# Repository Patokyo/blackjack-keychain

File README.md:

# Blackjack Keychain

A credit-card-sized blackjack strategy trainer. An ATmega328P deals a
six-deck shoe, you answer each decision with the on-board buttons, and
the firmware marks every answer correct or incorrect against basic
strategy before playing the hand out.

This is work in progress: the game logic and the serial log work, the
four-digit display and the LEDs are wired and mapped but not driven
yet.

## Repository layout

```
hardware/
  blackjack-keychain.kicad_pro      KiCad 10 project
  blackjack-keychain.kicad_sch      schematic, single sheet
  blackjack-keychain.kicad_pcb      board, 2 layer
  blackjack-keychain.net            netlist exported from the schematic
  fp-lib-table                      project footprint library table
  custom_footprint_library.pretty   project footprints (display, ISP pads)
  fabrication/                      gerbers, drills, job file, fab zip
firmware/
  blackjack-keychain/
    blackjack-keychain.ino        the sketch
  nano-blackjack/
    nano-blackjack.ino            the same game, remapped for a Nano
  nano-display-test/
    nano-display-test.ino         display wiring check for a Nano
virtual/
  index.html                        the board in a browser
  game.js, ui.js                    game engine, display and controls
  board-blue.svg, board-red.svg     front of the PCB, generated per mask colour
  make_board.py                     plots those from hardware/fabrication
```

The KiCad project, its netlist and its outputs stay together under
`hardware/` so the project opens with everything it needs in one
place. `hardware/fabrication/` holds the last set of outputs sent to
a board house; regenerating them means re-plotting from KiCad, not
editing them by hand. The virtual board is drawn from the same files:
`python3 virtual/make_board.py` re-plots `virtual/board-blue.svg` and
`virtual/board-red.svg` after a re-plot, so the browser keeps matching
the board.

## Hardware

| | |
|---|---|
| Board | 50 x 70 mm, 2 layer, 1.6 mm, 3.5 mm corner radius |
| MCU | ATmega328P-AU, TQFP-32, 5 V from USB-C, internal 8 MHz RC, no crystal |
| Display | CC56-12EWA, 0.28" four digit, common cathode, one NPN low side switch per digit |
| Indicators | 7 LEDs, active high through 330R |
| Input | 5 tactile buttons on two resistor ladders, plus SW6 as a strap |
| Programming | 2x03 ISP pads |

The board is powered from the USB-C socket. There is no USB-serial
chip on it, so the ISP pads are the only way to program it.

Pin map, as used by the firmware:

| Function | Pin | Pad |
|---|---|---|
| Correct / wrong / lose / push LEDs | D2 / D1 / D3 / D4 | 32 / 31 / 1 / 2 |
| Soft / pair / win LEDs | A1 / A3 / PB6 | 24 / 26 / 7 |
| Buttons, hit/stand/double ladder | A4 | 27 |
| Buttons, split/bank ladder | A5 | 28 |
| Display segments a-g, dp | D12, D6, D8, D11, D13, D10, D7, D9 | 16, 10, 12, 15, 17, 14, 11, 13 |
| Display digit drives Q1-Q4 | PB7, A0, D5, A2 | 8, 23, 9, 25 |
| SW6 strap | D0 | 30 |
| Serial TX | D1 (shared with the wrong LED) | 31 |

Two consequences of that netlist are worth knowing before flashing:
serial transmit shares a pin with an LED, so that LED glows between
bytes and flickers during output, and serial receive is held at +5 V or
GND by SW6, so the port cannot be typed into on an assembled board.
The buttons are the only input.

## Firmware

Open `firmware/blackjack-keychain/blackjack-keychain.ino` in the
Arduino IDE. The folder name matches the sketch name, as the IDE
requires.

- Build with `F_CPU = 8000000L` — MiniCore's ATmega328 at "8 MHz
  internal", or a Pro Mini 3.3 V/8 MHz board definition.
- Low fuse `0xE2`, with CKDIV8 unprogrammed. A part straight from the
  factory divides the internal oscillator down to 1 MHz, which plays
  the game eight times too slowly and garbles the serial output.
- Serial monitor at 9600 baud.

Rules: six deck shoe reshuffled between hands, dealer stands on soft
17, double on any first two cards, double after split allowed, up to
four hands by splitting (no resplitting aces, split aces get one card),
two card 21 is a natural that beats a made 21. Start with $100, a flat
$10 a hand, and the game ends when $10 can no longer be covered.

Controls are `H` (hit), `S` (stand), `D` (double) and `P` (split),
from the buttons or typed into the serial monitor if SW6 is left off
the board. The bank button is wired but has no game action yet.

## Building the hardware

The schematic and board reference one project-specific footprint
library, `custom_footprint_library`, which provides the 7 segment
display and the ISP pads. Both footprints are committed in
`hardware/custom_footprint_library.pretty/`, and `hardware/fp-lib-table`
maps the nickname onto that folder with `${KIPRJMOD}`, so the project
resolves them straight from a clone without any library setup.

To regenerate the outputs in `hardware/fabrication/`, plot from KiCad
with the same layer set currently committed: F.Cu, B.Cu, F.Paste,
B.Paste, F.Silkscreen, B.Silkscreen, F.Mask, B.Mask, Edge.Cuts, plus
the PTH and NPTH drill files.

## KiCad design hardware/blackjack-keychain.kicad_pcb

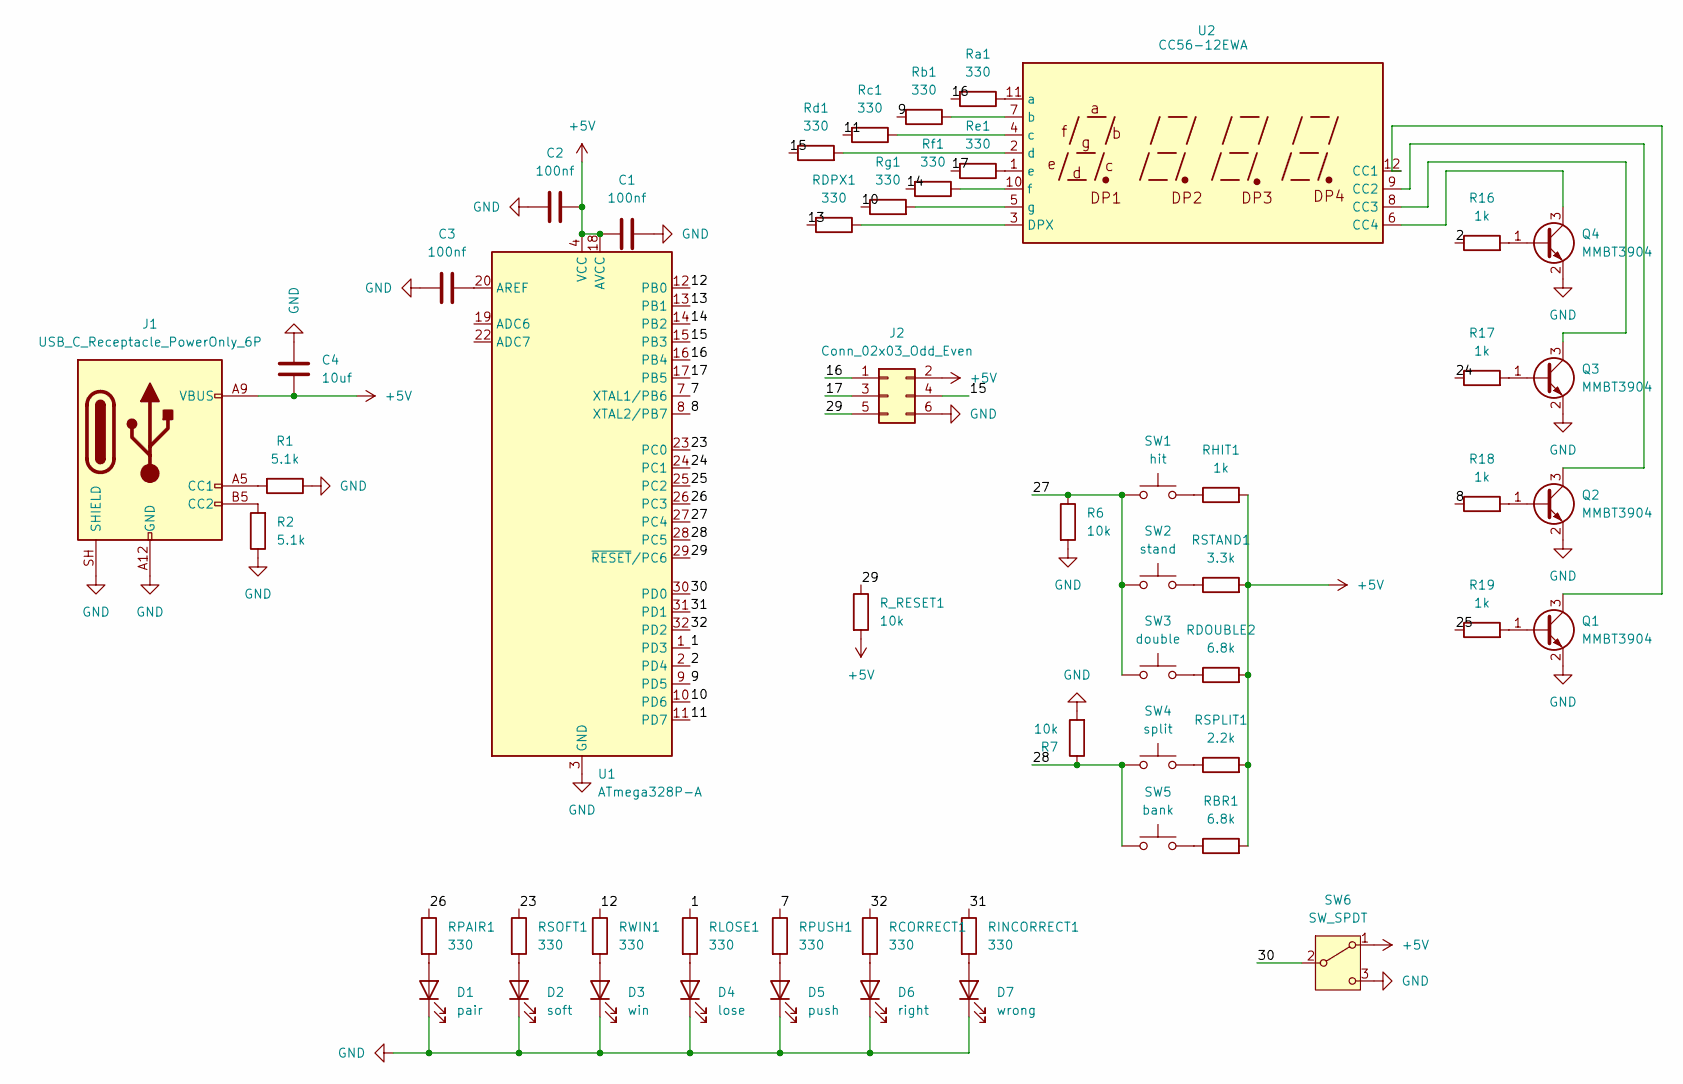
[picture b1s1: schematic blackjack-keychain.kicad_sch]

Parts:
C1, C2, C3: 100nf; C_0805_2012Metric_Pad1.18x1.45mm_HandSolder
C4: 10uf; C_0805_2012Metric_Pad1.18x1.45mm_HandSolder
D1: pair; LED_1210_3225Metric_Pad1.42x2.65mm_HandSolder
D2: soft; LED_1210_3225Metric_Pad1.42x2.65mm_HandSolder
D3: win; LED_1210_3225Metric_Pad1.42x2.65mm_HandSolder
D4: lose; LED_1210_3225Metric_Pad1.42x2.65mm_HandSolder
D5: push; LED_1210_3225Metric_Pad1.42x2.65mm_HandSolder
D6: right; LED_1210_3225Metric_Pad1.42x2.65mm_HandSolder
D7: wrong; LED_1210_3225Metric_Pad1.42x2.65mm_HandSolder
J1: USB_C_Receptacle_PowerOnly_6P; USB_C_Receptacle_GCT_USB4125-xx-x-0190_6P_TopMnt_Horizontal
J2: Conn_02x03_Odd_Even; ISP_2x03_Pads
Q1, Q2, Q3, Q4: MMBT3904; SOT-23
R1, R2: 5.1k; R_0805_2012Metric_Pad1.20x1.40mm_HandSolder
R6, R7: 10k; R_0805_2012Metric_Pad1.20x1.40mm_HandSolder
R16, R17, R18, R19: 1k; R_0805_2012Metric_Pad1.20x1.40mm_HandSolder
RBR1: 6.8k; R_0805_2012Metric_Pad1.20x1.40mm_HandSolder
RCORRECT1: 330; R_0805_2012Metric_Pad1.20x1.40mm_HandSolder
RDOUBLE2: 6.8k; R_0805_2012Metric_Pad1.20x1.40mm_HandSolder
RDPX1: 330; R_0805_2012Metric_Pad1.20x1.40mm_HandSolder
RHIT1: 1k; R_0805_2012Metric_Pad1.20x1.40mm_HandSolder
RINCORRECT1: 330; R_0805_2012Metric_Pad1.20x1.40mm_HandSolder
RLOSE1: 330; R_0805_2012Metric_Pad1.20x1.40mm_HandSolder
RPAIR1: 330; R_0805_2012Metric_Pad1.20x1.40mm_HandSolder
RPUSH1: 330; R_0805_2012Metric_Pad1.20x1.40mm_HandSolder
RSOFT1: 330; R_0805_2012Metric_Pad1.20x1.40mm_HandSolder
RSPLIT1: 2.2k; R_0805_2012Metric_Pad1.20x1.40mm_HandSolder
RSTAND1: 3.3k; R_0805_2012Metric_Pad1.20x1.40mm_HandSolder
RWIN1: 330; R_0805_2012Metric_Pad1.20x1.40mm_HandSolder
R_RESET1: 10k; R_0805_2012Metric_Pad1.20x1.40mm_HandSolder
Ra1: 330; R_0805_2012Metric_Pad1.20x1.40mm_HandSolder
Rb1: 330; R_0805_2012Metric_Pad1.20x1.40mm_HandSolder
Rc1: 330; R_0805_2012Metric_Pad1.20x1.40mm_HandSolder
Rd1: 330; R_0805_2012Metric_Pad1.20x1.40mm_HandSolder
Re1: 330; R_0805_2012Metric_Pad1.20x1.40mm_HandSolder
Rf1: 330; R_0805_2012Metric_Pad1.20x1.40mm_HandSolder
Rg1: 330; R_0805_2012Metric_Pad1.20x1.40mm_HandSolder
SW1: hit; SW_Tactile_SPST_NO_Straight_CK_PTS636Sx25SMTRLFS
SW2: stand; SW_Tactile_SPST_NO_Straight_CK_PTS636Sx25SMTRLFS
SW3: double; SW_Tactile_SPST_NO_Straight_CK_PTS636Sx25SMTRLFS
SW4: split; SW_Tactile_SPST_NO_Straight_CK_PTS636Sx25SMTRLFS
SW5: bank; SW_Tactile_SPST_NO_Straight_CK_PTS636Sx25SMTRLFS
SW6: SW_SPDT; SW_SPDT_Shouhan_MSK12C02
U1: ATmega328P-A; TQFP-32_7x7mm_P0.8mm
U2: CC56-12EWA; 7_Segment_Display-4_bit-0.28Inch

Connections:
+5V: C1.1, C2.1, C4.1, J1.A9 (VBUS), J1.B9 (VBUS), J2.2, RBR1.2, RDOUBLE2.2, RHIT1.2, RSPLIT1.2, RSTAND1.2, R_RESET1.2, SW6.1 (A), U1.4 (VCC), U1.6 (VCC), U1.18 (AVCC)
/1: RLOSE1.1, U1.1 (PD3)
/2: R16.1, U1.2 (PD4)
/7: RPUSH1.1, U1.7 (XTAL1/PB6)
/8: R18.1, U1.8 (XTAL2/PB7)
/9: Rb1.2, U1.9 (PD5)
/10: Rg1.1, U1.10 (PD6)
/11: Rc1.2, U1.11 (PD7)
/12: RWIN1.1, U1.12 (PB0)
/13: RDPX1.2, U1.13 (PB1)
/14: Rf1.2, U1.14 (PB2)
/15: J2.4, Rd1.1, U1.15 (PB3)
/16: J2.1, Ra1.2, U1.16 (PB4)
/17: J2.3, Re1.2, U1.17 (PB5)
/23: RSOFT1.1, U1.23 (PC0)
/24: R17.1, U1.24 (PC1)
/25: R19.1, U1.25 (PC2)
/26: RPAIR1.1, U1.26 (PC3)
/27: R6.1, SW1.1, SW2.1, SW3.1, U1.27 (PC4)
/28: R7.1, SW4.1, SW5.1, U1.28 (PC5)
/29: J2.5, R_RESET1.1, U1.29 (~RESET/PC6)
/30: SW6.2 (B), U1.30 (PD0)
/31: RINCORRECT1.1, U1.31 (PD1)
/32: RCORRECT1.1, U1.32 (PD2)
GND: C1.2, C2.2, C3.2, C4.2, D1.1 (K), D2.1 (K), D3.1 (K), D4.1 (K), D5.1 (K), D6.1 (K), D7.1 (K), J1.A12 (GND), J1.B12 (GND), J1.SH (SHIELD), J2.6, Q1.2 (E), Q2.2 (E), Q3.2 (E), Q4.2 (E), R1.1, R2.1, R6.2, R7.2, SW6.3 (C), U1.3 (GND), U1.5 (GND), U1.21 (GND)
unnamed: D1.2 (A), RPAIR1.2
unnamed: D2.2 (A), RSOFT1.2
unnamed: D3.2 (A), RWIN1.2
unnamed: D4.2 (A), RLOSE1.2
unnamed: D5.2 (A), RPUSH1.2
unnamed: D6.2 (A), RCORRECT1.2
unnamed: D7.2 (A), RINCORRECT1.2
unnamed: J1.A5 (CC1), R1.2
unnamed: J1.B5 (CC2), R2.2
unnamed: Q1.1 (B), R19.2
unnamed: Q1.3 (C), U2.12 (CC1)
unnamed: Q2.1 (B), R18.2
unnamed: Q2.3 (C), U2.9 (CC2)
unnamed: Q3.1 (B), R17.2
unnamed: Q3.3 (C), U2.8 (CC3)
unnamed: Q4.1 (B), R16.2
unnamed: Q4.3 (C), U2.6 (CC4)
unnamed: RBR1.1, SW5.2
unnamed: RDOUBLE2.1, SW3.2
unnamed: RHIT1.1, SW1.2
unnamed: RSPLIT1.1, SW4.2
unnamed: RSTAND1.1, SW2.2
unnamed: C3.1, U1.20 (AREF)
unnamed: RDPX1.1, U2.3 (DPX)
unnamed: Ra1.1, U2.11 (a)
unnamed: Rb1.1, U2.7 (b)
unnamed: Rc1.1, U2.4 (c)
unnamed: Rd1.2, U2.2 (d)
unnamed: Re1.1, U2.1 (e)
unnamed: Rf1.1, U2.10 (f)
unnamed: Rg1.2, U2.5 (g)

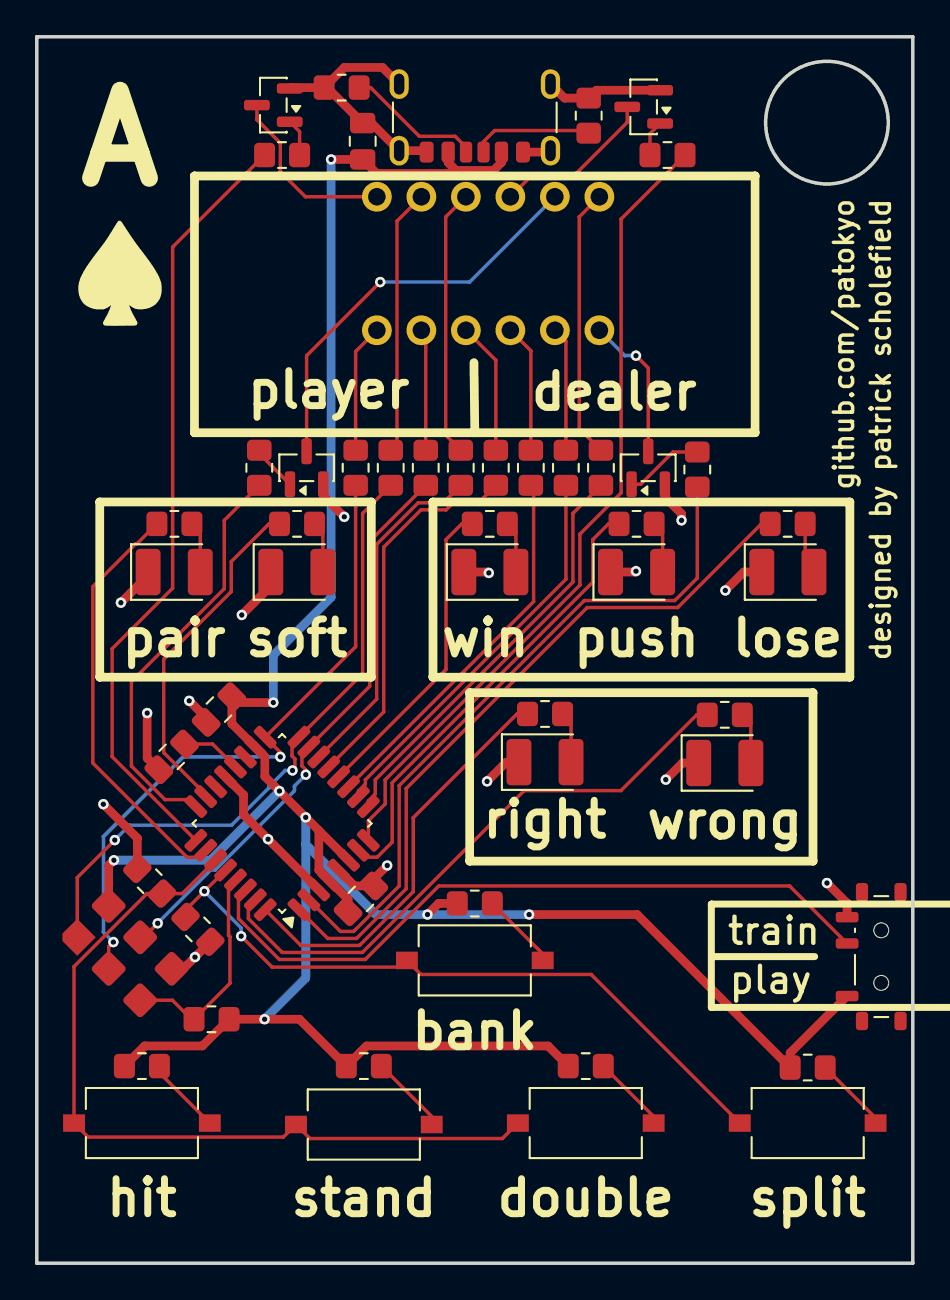
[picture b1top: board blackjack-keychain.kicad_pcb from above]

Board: 2 copper layers, 50.0 x 70.0 mm, 54 parts (0 on the bottom side), 56 nets.

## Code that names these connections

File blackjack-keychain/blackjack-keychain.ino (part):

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  TQFP pad, the second column the port bit, the third the Arduino
  name):

    pad 32  PD2  D2    correct LED
    pad 31  PD1  D1    wrong LED
    pad 30  PD0  D0    SW6, the mode switch, +5 V or GND
    pad  1  PD3  D3    lose LED
    pad  2  PD4  D4    push LED
    pad  9  PD5  D5    digit 3 driver, Q3
    pad 10  PD6  D6    segment b
    pad 11  PD7  D7    segment g
    pad 12  PB0  D8    segment c
    pad 13  PB1  D9    segment dp
    pad 14  PB2  D10   segment f
    pad 15  PB3  D11   segment d   (also ISP MOSI)
    pad 16  PB4  D12   segment a   (also ISP MISO)
    pad 17  PB5  D13   segment e   (also ISP SCK)
    pad 23  PC0  A0    digit 2 driver, Q2
    pad 24  PC1  A1    soft LED
    pad 25  PC2  A2    digit 4 driver, Q4
    pad 26  PC3  A3    pair LED
    pad 27  PC4  A4    hit / stand / double ladder
    pad 28  PC5  A5    split / bank ladder
    pad 29  PC6  RESET
    pad  7  PB6  ---   win LED
    pad  8  PB7  ---   digit 1 driver, Q1

  PB6 and PB7 have no Arduino number on a 328P, because a standard
  board spends them on the crystal. Here the chip runs from its
  internal oscillator, so they are free, but they can only be
  reached through PORTB:
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// --------------------------------------------------

// Mode switch, +5 V for play, GND for train
const int MODE_PIN = 0;        // PD0 pad 30

// Button ladders
const int BTN_MAIN_PIN = A4;   // PC4 pad 27: hit, stand, double
const int BTN_SIDE_PIN = A5;   // PC5 pad 28: split, bank

// LEDs, all active high through 330R
const int LED_PAIR    = A3;    // PC3 pad 26
const int LED_SOFT    = A1;    // PC1 pad 24
const int LED_LOSE    = 3;     // PD3 pad 1
const int LED_PUSH    = 4;     // PD4 pad 2
const int LED_CORRECT = 2;     // PD2 pad 32
const int LED_WRONG   = 1;     // PD1 pad 31
const byte LED_WIN_BIT = 6;    // PB6 pad 7, PORTB only

// Four digit display U2, CC56-12EWA, common cathode, with one NPN
// low side switch per digit. Segments and digit drives are all
// active high.
const int SEG_A  = 12;   // PB4 pad 16
const int SEG_B  = 6;    // PD6 pad 10
const int SEG_C  = 8;    // PB0 pad 12
const int SEG_D  = 11;   // PB3 pad 15
const int SEG_E  = 13;   // PB5 pad 17
const int SEG_F  = 10;   // PB2 pad 14
const int SEG_G  = 7;    // PD7 pad 11
const int SEG_DP = 9;    // PB1 pad 13

const int DIGIT_2 = A0;  // PC0 pad 23, Q2
const int DIGIT_3 = 5;   // PD5 pad 9,  Q3
const int DIGIT_4 = A2;  // PC2 pad 25, Q4
const byte DIGIT_1_BIT = 7;    // PB7 pad 8, Q1, PORTB only

// Segment order for the font table below
const byte SEG_PIN[7] = { SEG_A, SEG_B, SEG_C, SEG_D, SEG_E, SEG_F, SEG_G };
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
